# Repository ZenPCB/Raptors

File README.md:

# Raptors
387MHz to 464Mhz transceiver USB dongle

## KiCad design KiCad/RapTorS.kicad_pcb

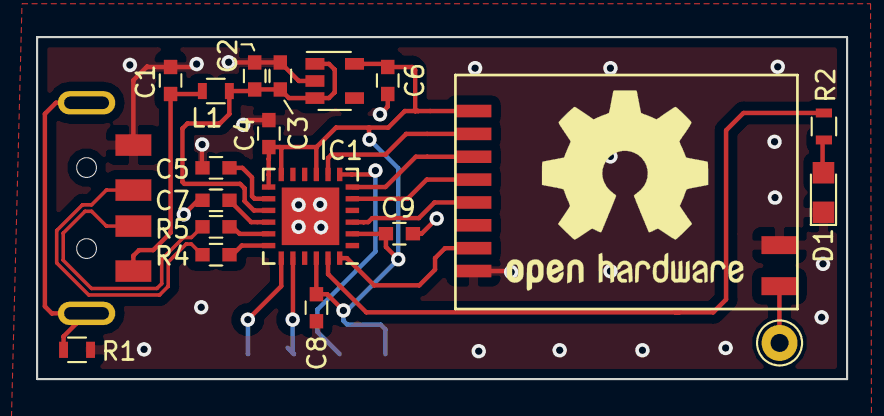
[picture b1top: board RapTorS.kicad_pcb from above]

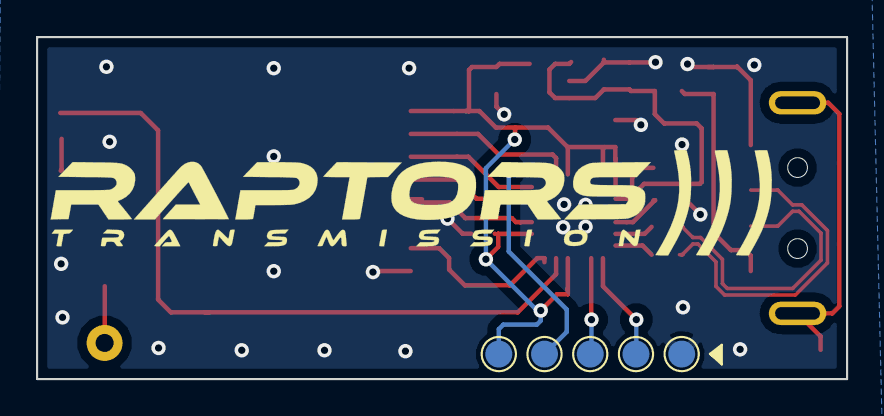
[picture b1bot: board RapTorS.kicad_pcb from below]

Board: 2 copper layers, 45.0 x 19.0 mm, 26 parts (6 on the bottom side), 23 nets.

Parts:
ANT1: antenna_433Mhz; Pin_d1.0mm_L10.0mm
C1: 10nF; C_0603
C2, C4, C6: 100nF; C_0603
C3: 4.7uF; C_0603
C5, C7, C8, C9: 1uF; C_0603
D1: LED_ALT; LED_0805
IC1: EFM32HG308F64G-A-QFN24; QFN-24-1EP_5x5mm_Pitch0.65mm
J1: Molex 48037-2200; MOLEX_USB_48037-2200
J2, J3, J4, J5, J6: TestPoint; Test_Point_Pad_d1.5mm
L1: 33R; L_0603
R1: 1M; R_0603
R2: 39R; R_0603
R4, R5: 15R; C_0603
RAPTORS: LOGO; Logo
U2: TLV71333PDBV; SOT-23-5
U3: E07-M1101S

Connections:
+3V3: C4.1, C6.1, C8.2, C9.2, IC1.2, IC1.9, IC1.12, IC1.13, IC1.22, J3.1, U2.5, U3.1
+5V: C2.1, C3.1, IC1.15, L1.2, U2.1, U2.3
CSN: IC1.6, U3.3
D+: J1.3, R4.2
D-: J1.2, R5.1
GDO0: IC1.8, U3.2
GDO2: IC1.24, U3.7
GND: C1.2, C2.2, C3.2, C4.2, C5.2, C6.2, C7.2, C8.1, C9.1, D1.1, IC1.25, J1.4, J4.1, R1.2, U2.2, U3.8, U3.10
LED: IC1.23, R2.1
MISO: IC1.4, U3.6
MOSI: IC1.3, U3.5
unnamed: ANT1.1, U3.9
unnamed: C1.1, J1.1, L1.1
unnamed: C5.1, IC1.14
unnamed: C7.1, IC1.16
unnamed: D1.2, R2.2
unnamed: IC1.17, R5.2
unnamed: IC1.18, R4.1
unnamed: J1.5, R1.1
SCK: IC1.5, U3.4
SWCLK: IC1.19, J6.1
SWDIO: IC1.20, J5.1
~RESET: IC1.7, J2.1

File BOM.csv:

Block;Footprint;Annotation;Description;Ref.;Farnell ref.;Quantity
USB;;J1;USB Connector;Molex 48037-2200;2313729;1
USB;0603;R1;1M resistor;generic;2861882;1
USB;0603;C1;10nF ceramic capacitor;generic;2896417;1
USB;0603;L1;33R ferrite bead;generic;1515742;1
USB;0603;C2, C4, C6;100nF ceramic capacitor;generic;2429362;3
USB;0603;C3;4.7uF ceramic capacitor;;9402128;1
PSU;SOT-23;U2;3.3V LDO;TLV71333PDBVR;2463932;1
LEDS;0603;R2;TBD;;TBD;1
LEDS;0805;D1;yellow LED;generic;1581241;1
RADIO;;U3;radio module;E07-M1101S;;1
RADIO;;ANT1;Antenna;TBD;TBD;1
CPU;QFN24;IC1;ARM Cortex M0;EFM32HG308;2475983;1
CPU;0603;C5, C7, C8, C9;1uF ceramic capacitor;generic;2896410;4
CPU;0603;R4, R5;15R resistor;generic;1652841;2

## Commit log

2018-03-15 inital commit, blank project
2018-08-01 add imported Si4012 component lib
2018-08-22 new schematic with new version of KiCad and new E07 radio module
2018-08-22 annotate schematic
2018-08-22 set values for USB block
2018-08-22 set values for CPU block
2018-08-22 set values for PSU block
2018-08-22 every values OK
2018-08-22 add E07 footprint, associate all footprints
2018-08-23 update USB connector ref
2018-08-28 finish USB footprint
2018-08-28 create PCB from schematic
2018-08-28 first placement
2018-08-28 placement second step
2018-08-29 routing OK
2018-08-30 add the logo
2018-08-30 update logo size
2018-08-30 update 3D models
2018-08-30 update 3D
2018-08-30 change C3 to ceramic, in order to fit in the case
2018-08-30 update C3 on layout, generate gerber
2018-08-30 add PCB dimentions
2018-08-30 change PCB dimentions layer
2018-09-01 odd OSHW logo
2018-09-10 add EFM32HG308 lib - add new uController on schematic
2018-09-10 routing completed
2018-09-11 add 3D shapes
2018-09-11 add missing footprint
2018-09-11 move KiCad related files inside KiCad folder
2018-09-12 correct pinout bug
2018-09-12 just move a via
2018-09-12 harmonize resistors and capacitors footprints due to KiCad issue #11
2018-09-12 refill zones
2018-09-12 update Gerber
2018-09-12 Update Readme picture
2018-09-18 add BOM with Farnell refs
2018-09-18 add Mouser ref
2019-05-13 update R2 to 50R
2019-05-13 update R2 to 56R (from E12 serie)
2019-09-19 add schematic PDF
2019-10-07 correct SPI pinout, add a led and a switch
2019-10-07 annotate new components
2019-10-07 change wire antenna by SMA connector
